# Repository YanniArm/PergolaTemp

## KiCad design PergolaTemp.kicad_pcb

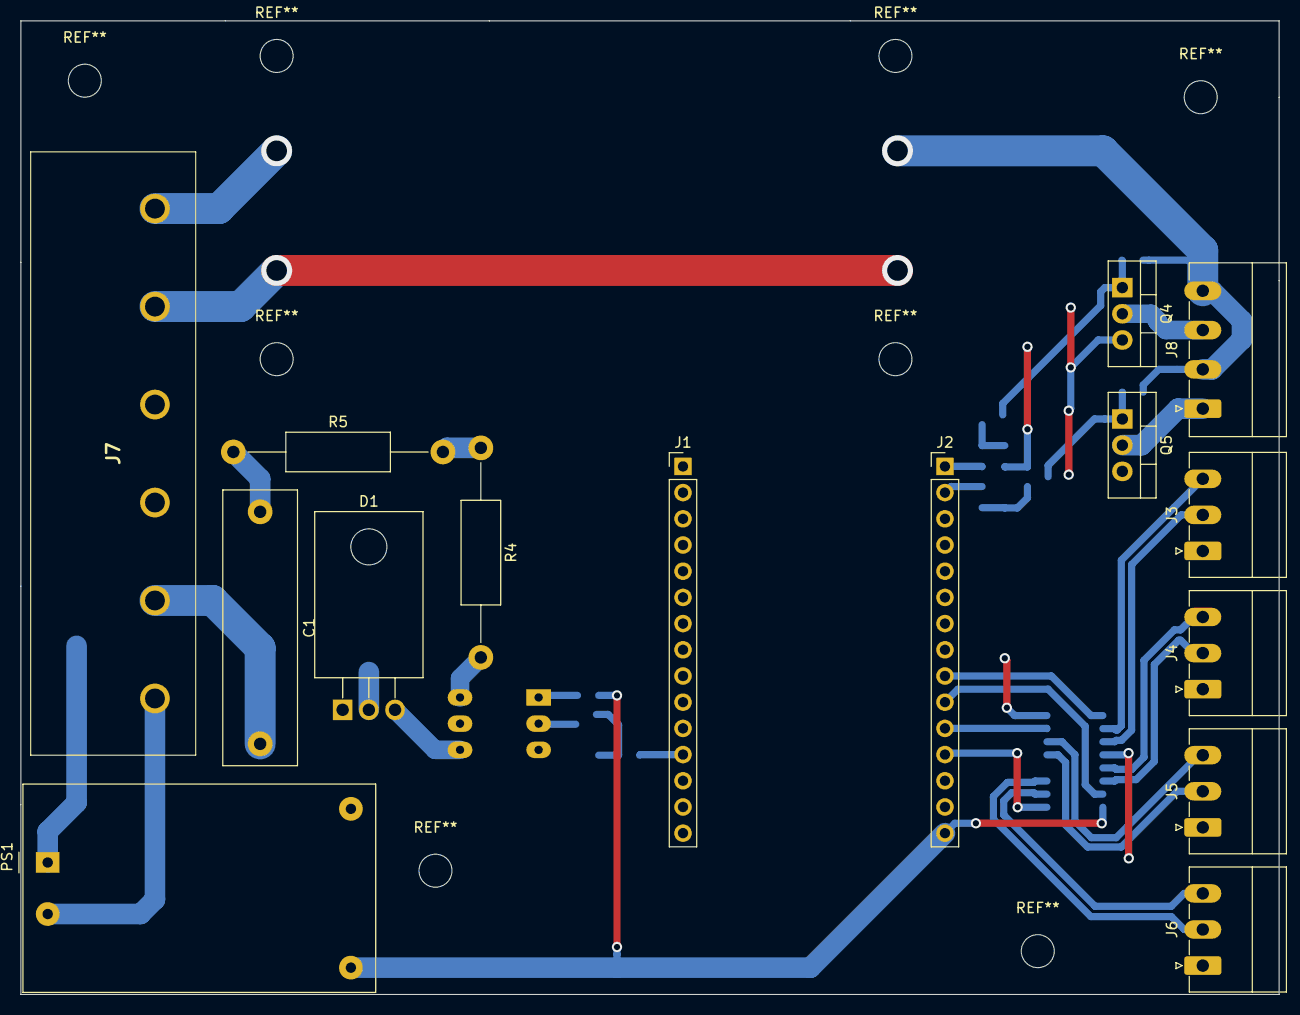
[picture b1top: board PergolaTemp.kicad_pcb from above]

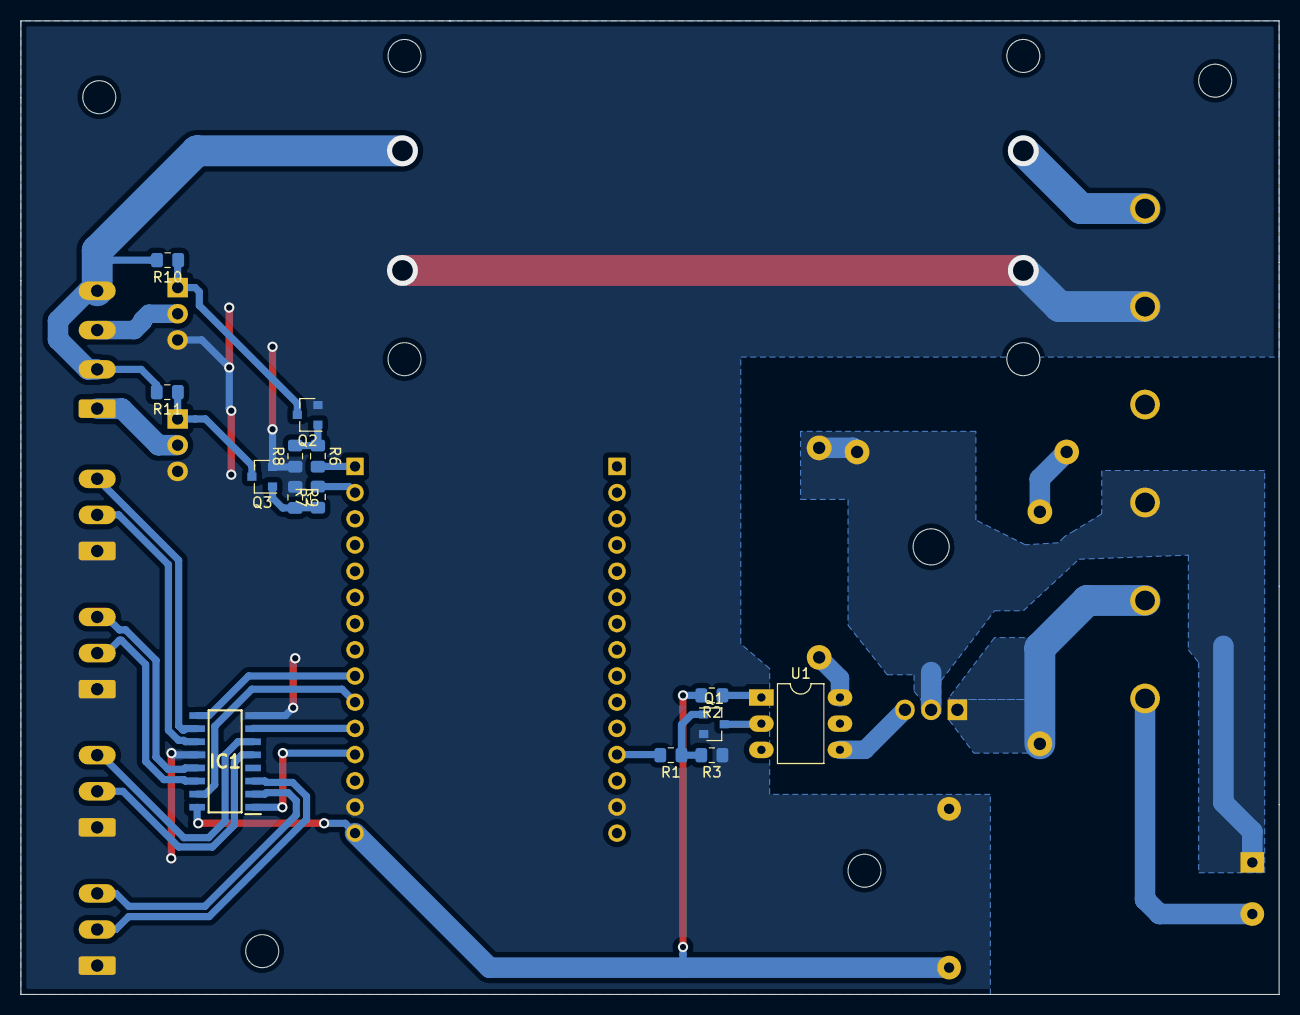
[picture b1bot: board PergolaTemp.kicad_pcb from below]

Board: 2 copper layers, 122.0 x 94.4 mm, 29 parts (14 on the bottom side), 33 nets.

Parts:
C1: CP; C_Rect_L26.5mm_W7.0mm_P22.50mm_MKS4
D1: Q_TRIAC_A1A2G; TO-220F-3_Horizontal_TabDown
IC1: AM26LV31CDRE4; SOIC127P600X175-16N
J1, J2: Conn_01x15_Female; PinHeader_1x15_P2.54mm_Vertical
J3, J4, J5, J6: Conn_01x03_Male; PhoenixContact_MC_1,5_3-G-3.5_1x03_P3.50mm_Horizontal
J7: Conn_01x06_Female; HB9500M956P
J8: Conn_01x04_Male; PhoenixContact_MC_1,5_4-G-3.81_1x04_P3.81mm_Horizontal
PS1: HLK-PM03; Converter_ACDC_HiLink_HLK-PMxx
Q1, Q2, Q3: BSS123; SOT-23
Q4, Q5: IRLZ44N; TO-220-3_Vertical
R1, R2, R3, R6, R7, R8, R9, R10, R11: R; R_0805_2012Metric_Pad1.15x1.40mm_HandSolder
R4, R5: R; R_Axial_DIN0411_L9.9mm_D3.6mm_P20.32mm_Horizontal
U1: MOC3063M; DIP-6_W7.62mm_LongPads

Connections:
+3V3: IC1.16, J2.15, PS1.4, R2.2
+24V: J8.2, J8.4, R10.2, R11.2
AC: D1.2, J7.4, PS1.1, R4.1, R5.2
AC_N: J7.6, PS1.2
GND: IC1.8, IC1.12, J1.14, J2.14, J3.1, J4.1, J5.1, J6.1, J7.2, PS1.3, Q1.2, Q2.2, Q3.2, Q4.3, Q5.3, R3.1, R8.1, R9.1
L_SWITCH: C1.2, D1.1, J7.5
unnamed: C1.1, R5.1
unnamed: D1.3, U1.4
unnamed: J8.1, Q5.2
unnamed: J8.3, Q4.2
unnamed: Q1.1, R1.1, R3.2
unnamed: Q1.3, U1.2
unnamed: Q2.1, R6.1, R8.2
unnamed: Q2.3, Q4.1, R10.1
unnamed: Q3.1, R7.1, R9.2
unnamed: Q3.3, Q5.1, R11.1
unnamed: R2.1, U1.1
unnamed: R4.2, U1.6
OUT1+: IC1.2, J6.3
OUT1-: IC1.3, J6.2
OUT2+: IC1.6, J5.3
OUT2-: IC1.5, J5.2
OUT3+: IC1.10, J3.3
OUT3-: IC1.11, J3.2
OUT4+: IC1.14, J4.2
OUT4-: IC1.13, J4.3
POWER_SWITCH: J1.12, R1.2
STRIP1: IC1.1, J2.12
STRIP2: IC1.7, J2.11
STRIP3: IC1.15, J2.10
STRIP4: IC1.9, J2.9
WHITE1: J2.1, R6.2
WHITE2: J2.2, R7.2
